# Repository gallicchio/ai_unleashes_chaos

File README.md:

# AI UNLEASHES CHAOS

[Lorenz Attractor Circuit](https://seti.harvard.edu/unusual_stuff/misc/lorenz.htm) by Paul Horowitz in KiCAD

"Claude, I want you to build a nice little present for Paul Horowitz, which could also live on as an open source project and a kit that people could build. Make a KiCAD 10 project, schematic, and PCB to implement [Paul's Lorenz Attractor Circuit](https://seti.harvard.edu/unusual_stuff/misc/lorenz.htm)."

<!-- GitHub strips <iframe> from READMEs, so a video cannot play in place;
     this is the thumbnail with a play button, linked to YouTube. -->
<p align="center">
  
  <br>
  <a href="https://youtu.be/pzk5cd-qo5U"><b>&#9654; Watch on YouTube</b></a>
</p>

<!-- GitHub will not play a video stored in the repository inline in a README,
     so this is an animated GIF of it, linked to the clip itself. -->
<p align="center">
  
  <br>
  <a href="docs/images/20261106_154352_video_analog_scope.mp4?raw=true"><b>&#9654; Download the scope video (9 MB mp4)</b></a>
</p>

In graduate school I worked with Paul Horowitz, of [Art of Electronics](https://artofelectronics.net/) fame. I even contributed a few bits and pieces to the 3rd edition. (I am thanked in the footnotes, one of which simply says, "Jason, again.") This project started by [asking Claude](CLAUDE_CODE_CHAT.md) the above question. Watch his reaction above. Also watch Paul's [Interview with Ladyada](https://www.youtube.com/watch?v=iCI3B5eT9NA) to get a sense for the guy.

**Only Prompts:**
As an experiment, the entire PCB, along with additions to Paul's original circuit were designed in a few
hours of [prompts to Claude Opus 5 Max](CLAUDE_CODE_CHAT.md). I only typed prompts.
I only used KiCAD to look at the output of Claude's [python scripts](scripts/), which generated everything else.

## What it is

A 100 x 100 mm, two-layer, USB-C-powered analog computer that solves

    dx/dt = s (y - x)          s = 10
    dy/dt = r x - y - x z      r = 21.3 .. 37.0, on a knob
    dz/dt = x y - b z          b = 8/3

in real time, continuously, with three op-amp integrators and two **MPY634**
analog multipliers — Paul's exact parts, in hand-solderable packages, so the
circuit stays literally his. Hang a scope on `x` and `z` in X-Y and the
attractor's "owl's face" appears within a second of power-up.

**Fun additions to Paul's original circuit:**

* **Four speeds on a DIP switch** — `fast!` (τ = 2.2 ms) through `slower!`
  (572 ms), the six sliders reading left to right as a two-digit binary
  number. At `slower!` you can follow the dot around a wing by eye.
* **An r knob.** 21.3 to 37.0 on a single-turn trimmer, which takes you from
  "the trace spirals into one wing and stops" through the bistable window at
  r ≈ 24.1–24.7 and Lorenz's own 28, to a tight fast orbit at 37. Its wiper is
  tied to one end of the track on purpose: grit under a wiper then means
  *maximum resistance*, never an open circuit.
* **A chaos lamp.** One RGB LED whose colour is the state vector. Red
  follows −y, green x and blue z, and two more resistors pull red's and
  blue's thresholds apart so the dies take turns instead of mixing to
  white: it is vivid nine-tenths of the time and visits every hue about
  equally. Rev A's lamp was picked from [660 rendered wirings](docs/lamp/)
  with an LED model the boards then proved wrong — it came out mostly blue —
  so rev B's was chosen again with a corrected model, from 6.7 million
  wirings; [the ten finalists play in real time](docs/lamp2/).
* **A real isolated ground split.** The DC/DC converter's isolation is
  actually used: analog ground and USB ground are separate pours with a 1 mm
  gap, bridged only by 1 M, 2.2 nF and a solder jumper, so no mains-referenced
  loop runs through a signal whose full scale is 2 V.
* **`SYNC IN X`.** A fourth BNC and a weight knob: feed it another board's `x`
  output and the two boards synchronise — chaotic synchronisation on the
  bench. Pull
  the cable and they diverge again from states that agreed to a few
  millivolts. The knob is linear in coupling strength from 0 to 10, with the
  locking threshold at about 70 % of rotation.
**Everything here is generated.** There is no hand-edited schematic or board:
`./make.py` writes the symbols, footprints, 3D models, schematic, placement,
routing, silkscreen, gerbers, BOM and CPL from Python, and then checks them.
147 circuit assertions read the exported netlist back and re-derive the
equations from the resistors that are really attached, and simulate the lamp
the netlist really builds; the QR codes on the
back are decoded out of the gerbers they were plotted into; and a clean clone
rebuilds every deliverable byte-identically.

The back carries the equations, the owl's face drawn from a real integration
of them, and QR codes to Paul's page and to this repository.

## Building it

Needs KiCad 10, and Python 3 with `numpy` and `Pillow`; `pdftoppm`
(poppler-utils) for the preview images.

```bash
git clone https://github.com/gallicchio/ai_unleashes_chaos.git

cd ai_unleashes_chaos

# Nothing to configure if kicad-cli is on your PATH, or if a KiCad 10
# AppImage is in ~/.local/bin, ~/Downloads, ~/Applications, ~/bin or /opt:
# the build finds it and mounts it for as long as it runs.  Otherwise:
export KICAD_APPIMAGE=$HOME/.local/bin/kicad-10.0.6-x86_64.AppImage
# ...or, for an AppImage you have already extracted:
# export KICAD_APPRUN=$HOME/.local/kicad10/AppDir/AppRun

./make.py                # build and check everything  (~40 s)
./make.py --clean        # delete everything it generates
```

Upload `out/lorenz/lorenz-gerbers.zip` and `-bom.csv` to a fab, with
`-cpl_jlc_corrected.csv` for the placements if that fab is JLCPCB and
`-cpl.csv` if it is anyone else — JLCPCB turns six of the parts differently
from KiCad, and the corrected file is the same placements with those angles
applied. Read **[docs/MANUFACTURING.md](docs/MANUFACTURING.md)** first: it
lists what to check in the fab's preview before you pay.

## More

* **[docs/DESIGN_NOTES.md](docs/DESIGN_NOTES.md)** — the circuit, every
  changed value and why, and how the lamp was chosen.
* **[docs/DESIGN_REVIEW.md](docs/DESIGN_REVIEW.md)** — the design reviews,
  including the bugs the checks caught.
* **[CLAUDE_CODE_CHAT.md](CLAUDE_CODE_CHAT.md)** — the entire conversation
  that produced this board, prompt by prompt.

Circuit by Paul Horowitz. Board by Jason Gallicchio and Claude Opus 5 Max.

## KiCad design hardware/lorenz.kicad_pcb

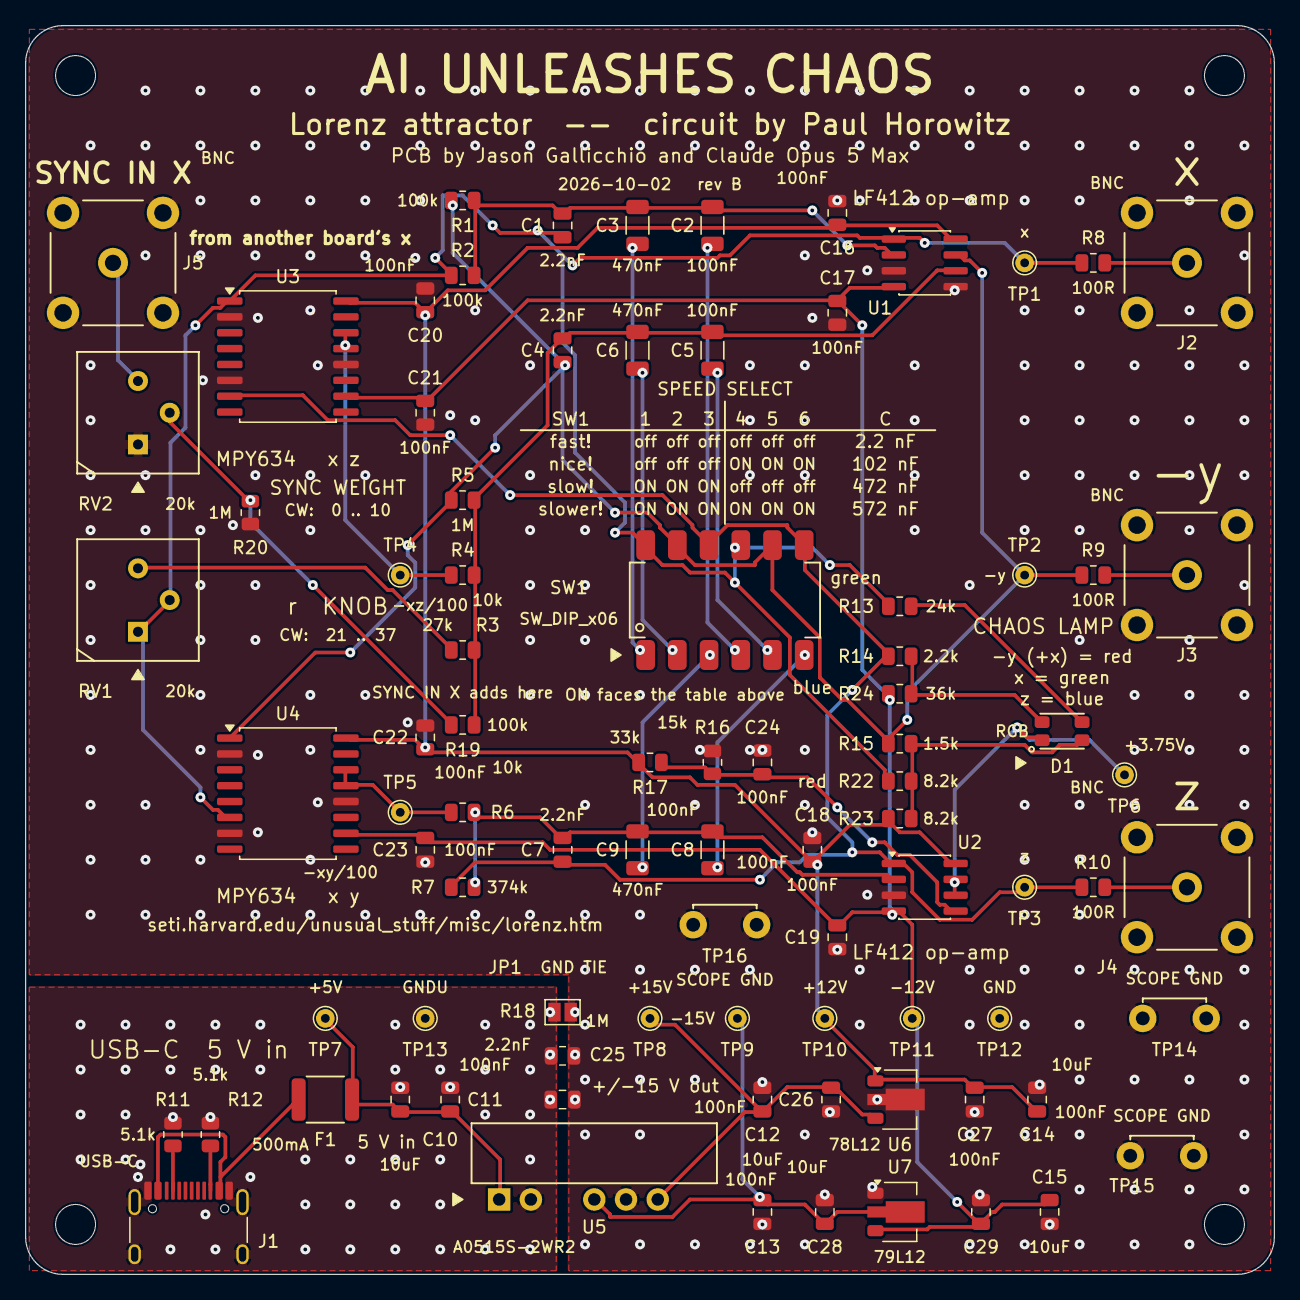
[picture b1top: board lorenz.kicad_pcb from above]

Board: 2 copper layers, 100.0 x 100.0 mm, 90 parts (0 on the bottom side), 35 nets.

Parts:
C1, C4, C7, C25: 2.2nF; C_0805_2012Metric
C2, C5, C8: 100nF; C_1206_3216Metric
C3, C6, C9: 470nF; C_1206_3216Metric
C10, C12, C13, C14, C15: 10uF; C_0805_2012Metric
C11, C16, C17, C18, C19, C20, C21, C22, C23, C24, C26, C27, C28, C29: 100nF; C_0805_2012Metric
D1: RGB; LED_RGB_PLCC4_3.5x2.8mm
F1: 500mA; PTC_1812_4532Metric
J1: USB-C; USB_C_Receptacle_HRO_TYPE-C-31-M-12
J2, J3, J4, J5: BNC; BNC_KYWE_RightAngle
JP1: GND TIE; SolderJumper-2_P1.3mm_Open_Pad1.0x1.5mm
MH1, MH2, MH3, MH4: MountingHole; MountingHole_3.2mm_M3
R1, R2, R19: 100k; R_0805_2012Metric
R3: 27k; R_0805_2012Metric
R4, R6: 10k; R_0805_2012Metric
R5, R18, R20: 1M; R_0805_2012Metric
R7: 374k; R_0805_2012Metric
R8, R9, R10: 100R; R_0805_2012Metric
R11, R12: 5.1k; R_0805_2012Metric
R13: 24k; R_0805_2012Metric
R14: 2.2k; R_0805_2012Metric
R15: 1.5k; R_0805_2012Metric
R16: 15k; R_0805_2012Metric
R17: 33k; R_0805_2012Metric
R22, R23: 8.2k; R_0805_2012Metric
R24: 36k; R_0805_2012Metric
RV1, RV2: 20k; Potentiometer_Bourns_3386P_Vertical
SW1: SW_DIP_x06; SW_DIP_SPSTx06_KingTek_DSIC06_P2.54mm
TP1: x; TestPoint_THTPad_D1.5mm_Drill0.7mm
TP2: -y; TestPoint_THTPad_D1.5mm_Drill0.7mm
TP3: z; TestPoint_THTPad_D1.5mm_Drill0.7mm
TP4: -xz/100; TestPoint_THTPad_D1.5mm_Drill0.7mm
TP5: -xy/100; TestPoint_THTPad_D1.5mm_Drill0.7mm
TP6: +3.75V; TestPoint_THTPad_D1.5mm_Drill0.7mm
TP7: +5V; TestPoint_THTPad_D1.5mm_Drill0.7mm
TP8: +15V; TestPoint_THTPad_D1.5mm_Drill0.7mm
TP9: -15V; TestPoint_THTPad_D1.5mm_Drill0.7mm
TP10: +12V; TestPoint_THTPad_D1.5mm_Drill0.7mm
TP11: -12V; TestPoint_THTPad_D1.5mm_Drill0.7mm
TP12: GND; TestPoint_THTPad_D1.5mm_Drill0.7mm
TP13: GNDU; TestPoint_THTPad_D1.5mm_Drill0.7mm
TP14, TP15, TP16: SCOPE GND; TestPoint_ScopeGnd_Loop_2x1.1mm
U1, U2: LF412; SOIC-8_3.9x4.9mm_P1.27mm
U3, U4: MPY634; SOIC-16W_7.5x10.3mm_P1.27mm
U5: A0515S-2WR2; DCDC_SIP_A05xxS_1W_2W
U6: 78L12; SOT-89-3
U7: 79L12; SOT-89-3

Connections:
+5V: C10.1, C11.1, F1.2, TP7.1, U5.1
+12V: C14.1, C16.1, C18.1, C20.1, C22.1, C27.2, R17.1, R23.2, TP10.1, U1.8, U2.8, U3.16, U4.16, U6.1
+15V: C12.1, C26.2, TP8.1, U5.6, U6.3
-12V: C15.2, C17.2, C19.2, C21.2, C23.2, C29.1, R24.2, TP11.1, U1.4, U2.4, U3.10, U4.10, U7.3
-15V: C13.2, C28.1, TP9.1, U5.4, U7.2
/-y: C4.1, R1.1, R5.1, R9.1, R15.2, SW1.8, SW1.11, TP2.1, U1.7, U4.1
/SJ_X: C1.2, C2.2, C3.2, R1.2, R2.2, U1.2
/SJ_Y: C4.2, C5.2, C6.2, R3.2, R4.2, R5.2, R19.2, U1.6
/SJ_Z: C7.2, C8.2, C9.2, R6.2, R7.2, U2.2
/x: C1.1, R2.1, R8.1, R13.2, R22.2, RV1.1, RV1.2, SW1.9, SW1.12, TP1.1, U1.1, U3.1, U4.6
/xy: R6.1, TP5.1, U4.13, U4.14
/xz: R4.1, TP4.1, U3.13, U3.14
/z: C7.1, R7.1, R10.1, R14.2, SW1.7, SW1.10, TP3.1, U2.1, U3.7
GND: C12.2, C13.1, C14.2, C15.1, C16.2, C17.1, C18.2, C19.1, C20.2, C21.1, C22.2, C23.1, C24.2, C25.2, C26.1, C27.1, C28.2, C29.2, J2.2, J3.2, J4.2, J5.2, JP1.2, R16.2, R18.2, R20.1, RV2.1, TP12.1, TP14.1, TP15.1, TP16.1, U1.3, U1.5, U2.3, U3.2, U3.6, U3.12, U4.2, U4.7, U4.12, U5.5, U6.2, U7.1
GNDU: C10.2, C11.2, C25.1, J1.A1, J1.A12, J1.B1, J1.B12, J1.SH, JP1.1, R11.2, R12.2, R18.1, TP13.1, U5.2
unnamed: C2.1, SW1.4
unnamed: C3.1, SW1.1
unnamed: C5.1, SW1.5
unnamed: C6.1, SW1.2
unnamed: C8.1, SW1.6
unnamed: C9.1, SW1.3
unnamed: D1.1, TP6.1, U2.6, U2.7
unnamed: D1.2, R14.1, R24.1
unnamed: D1.3, R13.1
unnamed: D1.4, R15.1, R22.1, R23.1
unnamed: F1.1, J1.A4, J1.A9, J1.B4, J1.B9
unnamed: J1.A5, R11.1
unnamed: J1.B5, R12.1
unnamed: J2.1, R8.2
unnamed: J3.1, R9.2
unnamed: J4.1, R10.2
unnamed: J5.1, RV2.3
unnamed: R3.1, RV1.3
unnamed: R19.1, R20.2, RV2.2
unnamed: C24.1, R16.1, R17.2, U2.5

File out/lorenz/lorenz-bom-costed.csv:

Comment,Designator,Footprint,LCSC Part #,MPN,Qty,Unit $,Ext $,JLC
100nF,"C2,C5,C8",C_1206_3216Metric,C170182,1206N104J500CT,3,0.1870,0.561,extended
470nF,"C3,C6,C9",C_1206_3216Metric,C277483,CC1206KKX7R9BB474,3,0.0320,0.096,extended
2.2nF,"C1,C4,C7,C25",C_0805_2012Metric,C28260,CL21C222JBFNNNE,4,0.0280,0.112,basic
10uF,"C10,C12,C13,C14,C15",C_0805_2012Metric,C15850,CL21A106KAYNNNE,5,0.0840,0.420,basic
100nF,"C11,C16,C17,C18,C19,C20,C21,C22,C23,C24,C26,C27,C28,C29",C_0805_2012Metric,C49678,CC0805KRX7R9BB104,14,0.0190,0.266,basic
RGB,D1,LED_RGB_PLCC4_3.5x2.8mm,C2962095,MHPA3528CRGBCT,1,0.0650,0.065,extended
500mA,F1,PTC_1812_4532Metric,C17313,MF-MSMF050-2,1,0.0680,0.068,extended
USB-C,J1,USB_C_Receptacle_HRO_TYPE-C-31-M-12,C165948,TYPE-C-31-M-12,1,0.1860,0.186,extended
BNC,"J2,J3,J4,J5",BNC_KYWE_RightAngle,C41416668,BNC-KYWE-295-W4-N,4,1.5490,6.196,extended
27k,R3,R_0805_2012Metric,C17593,0805W8F2702T5E,1,0.0013,0.001,basic
374k,R7,R_0805_2012Metric,C2933427,FRC0805F3743TS,1,0.0040,0.004,extended
24k,R13,R_0805_2012Metric,C17575,0805W8F2402T5E,1,0.0021,0.002,basic
2.2k,R14,R_0805_2012Metric,C17520,0805W8F2201T5E,1,0.0021,0.002,basic
1.5k,R15,R_0805_2012Metric,C4310,0805W8F1501T5E,1,0.0015,0.002,basic
15k,R16,R_0805_2012Metric,C17475,0805W8F1502T5E,1,0.0021,0.002,basic
33k,R17,R_0805_2012Metric,C17633,0805W8F3302T5E,1,0.0028,0.003,basic
36k,R24,R_0805_2012Metric,C4360,0805W8F3602T5E,1,0.0029,0.003,basic
10k,"R4,R6",R_0805_2012Metric,C17414,0805W8F1002T5E,2,0.0040,0.008,basic
5.1k,"R11,R12",R_0805_2012Metric,C27834,0805W8F5101T5E,2,0.0060,0.012,basic
8.2k,"R22,R23",R_0805_2012Metric,C17828,0805W8F8201T5E,2,0.0021,0.004,basic
20k,"RV1,RV2",Potentiometer_Bourns_3386P_Vertical,C116287,3386P-1-203LF,2,0.4458,0.892,extended
100k,"R1,R2,R19",R_0805_2012Metric,C149504,0805W8F1003T5E,3,0.0060,0.018,basic
100R,"R8,R9,R10",R_0805_2012Metric,C17408,0805W8F1000T5E,3,0.0040,0.012,basic
1M,"R5,R18,R20",R_0805_2012Metric,C17514,0805W8F1004T5E,3,0.0050,0.015,basic
SW_DIP_x06,SW1,SW_DIP_SPSTx06_KingTek_DSIC06_P2.54mm,C54952,DSIC06LSGET,1,0.5710,0.571,extended
A0515S-2WR2,U5,DCDC_SIP_A05xxS_1W_2W,C19272710,A0515S-2WR2,1,1.5950,1.595,extended
78L12,U6,SOT-89-3,C8615,CJ78L12,1,0.0990,0.099,extended
79L12,U7,SOT-89-3,C8626,CJ79L12,1,0.1180,0.118,extended
LF412,"U1,U2",SOIC-8_3.9x4.9mm_P1.27mm,C15322,LF412CDR,2,0.9060,1.812,extended
MPY634,"U3,U4",SOIC-16W_7.5x10.3mm_P1.27mm,C1523457,MPY634KU/1K,2,30.5860,61.172,extended

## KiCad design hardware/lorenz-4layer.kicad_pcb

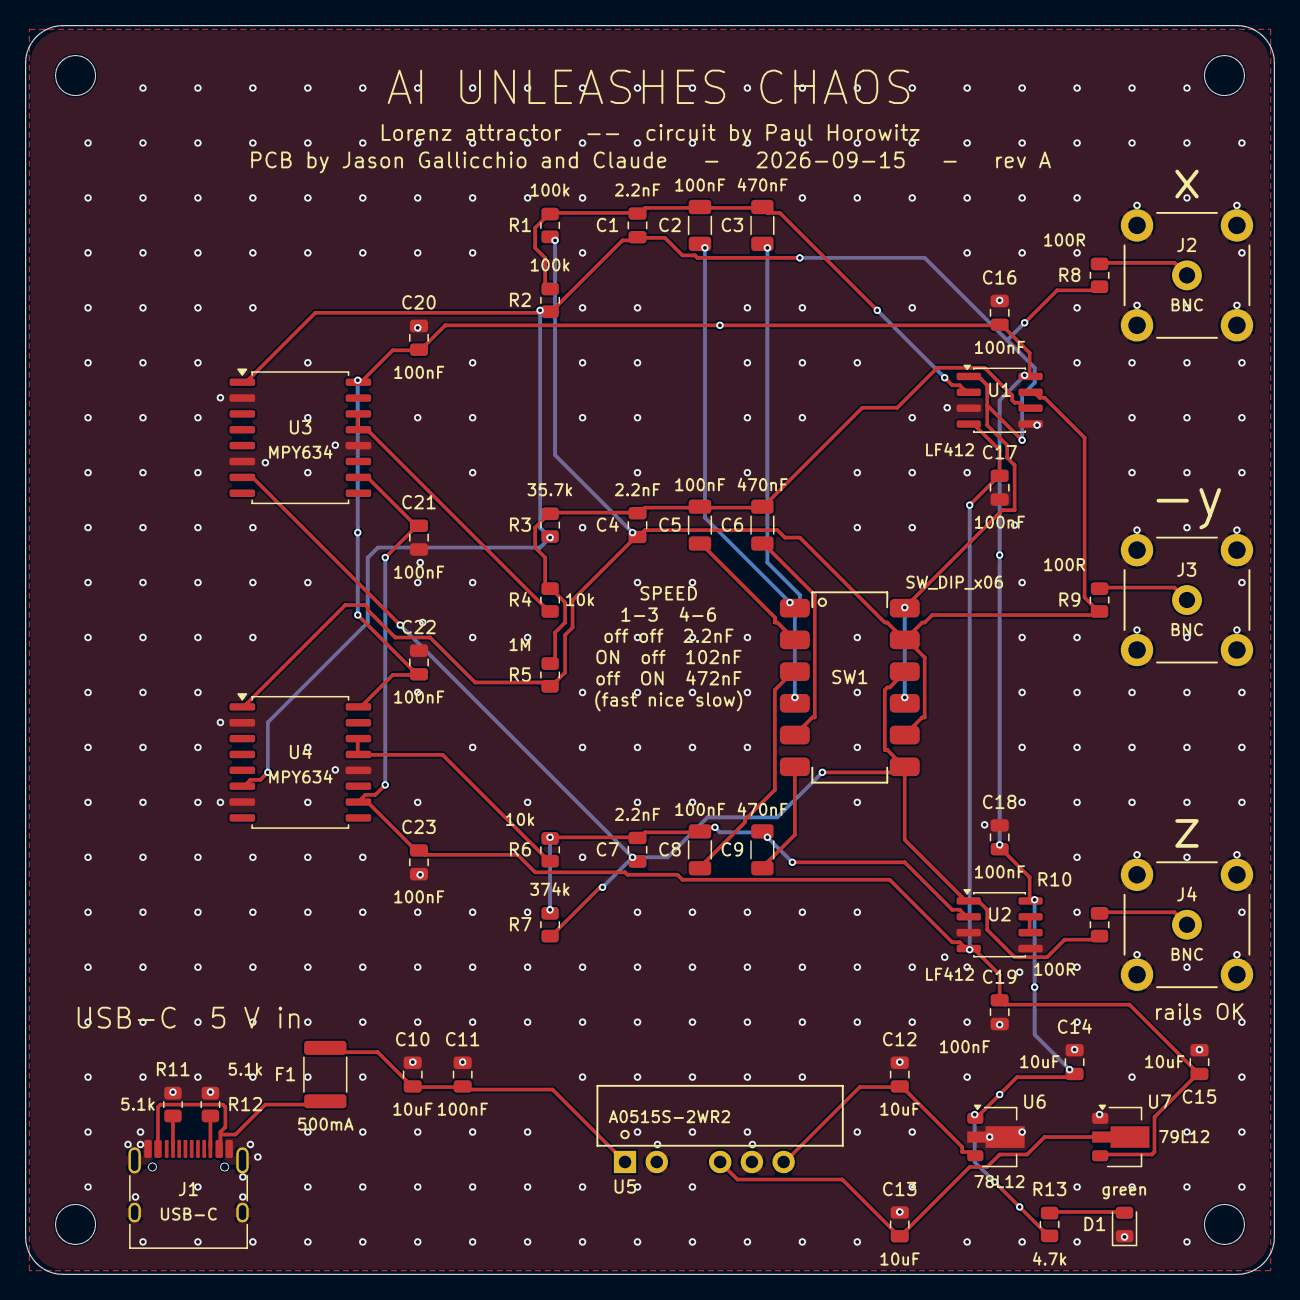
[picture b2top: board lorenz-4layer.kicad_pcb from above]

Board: 4 copper layers, 100.0 x 100.0 mm, 54 parts (0 on the bottom side), 28 nets.

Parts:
C1, C4, C7: 2.2nF; C_0805_2012Metric
C2, C5, C8: 100nF; C_1206_3216Metric
C3, C6, C9: 470nF; C_1206_3216Metric
C10, C12, C13, C14, C15: 10uF; C_0805_2012Metric
C11, C16, C17, C18, C19, C20, C21, C22, C23: 100nF; C_0805_2012Metric
D1: green; LED_0805_2012Metric
F1: 500mA; Fuse_1812_4532Metric
J1: USB-C; USB_C_Receptacle_HRO_TYPE-C-31-M-12
J2, J3, J4: BNC; BNC_KYWE_RightAngle
MH1, MH2, MH3, MH4: MountingHole; MountingHole_3.2mm_M3
R1, R2: 100k; R_0805_2012Metric
R3: 35.7k; R_0805_2012Metric
R4, R6: 10k; R_0805_2012Metric
R5: 1M; R_0805_2012Metric
R7: 374k; R_0805_2012Metric
R8, R9, R10: 100R; R_0805_2012Metric
R11, R12: 5.1k; R_0805_2012Metric
R13: 4.7k; R_0805_2012Metric
SW1: SW_DIP_x06; SW_DIP_SPSTx06_KingTek_DSIC06_P2.54mm
U1, U2: LF412; SOIC-8_3.9x4.9mm_P1.27mm
U3, U4: MPY634; SOIC-16W_7.5x10.3mm_P1.27mm
U5: A0515S-2WR2; DCDC_SIP_A05xxS_1W_2W
U6: 78L12; SOT-89-3
U7: 79L12; SOT-89-3

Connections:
+5V: C10.1, C11.1, F1.2, U5.1
+12V: C14.1, C16.1, C18.1, C20.1, C22.1, R13.1, U1.8, U2.8, U3.16, U4.16, U6.1
+15V: C12.1, U5.6, U6.3
-12V: C15.1, C17.2, C19.2, C21.2, C23.2, U1.4, U2.4, U3.10, U4.10, U7.3
-15V: C13.1, U5.4, U7.2
/-y: C4.1, R1.1, R5.1, R9.1, SW1.8, SW1.11, U1.7, U4.1
/x: C1.1, R2.1, R3.1, R8.1, SW1.9, SW1.12, U1.1, U3.1, U4.6
/xy: R6.1, U4.13, U4.14
/xz: R4.1, U3.13, U3.14
/z: C7.1, R7.1, R10.1, SW1.7, SW1.10, U2.1, U3.7
GND: C10.2, C11.2, C12.2, C13.2, C14.2, C15.2, C16.2, C17.1, C18.2, C19.1, C20.2, C21.1, C22.2, C23.1, D1.1, J1.A1, J1.A12, J1.B1, J1.B12, J1.SH, J2.2, J3.2, J4.2, R11.2, R12.2, U1.3, U1.5, U2.3, U2.5, U3.2, U3.6, U3.12, U4.2, U4.7, U4.12, U5.2, U5.5, U6.2, U7.1
unnamed: C2.1, SW1.1
unnamed: C3.1, SW1.4
unnamed: C5.1, SW1.2
unnamed: C6.1, SW1.5
unnamed: C8.1, SW1.3
unnamed: C9.1, SW1.6
unnamed: D1.2, R13.2
unnamed: F1.1, J1.A4, J1.A9, J1.B4, J1.B9
unnamed: J1.A5, R11.1
unnamed: J1.B5, R12.1
unnamed: J2.1, R8.2
unnamed: J3.1, R9.2
unnamed: J4.1, R10.2
unnamed: C1.2, C2.2, C3.2, R1.2, R2.2, U1.2
unnamed: C4.2, C5.2, C6.2, R3.2, R4.2, R5.2, U1.6
unnamed: C7.2, C8.2, C9.2, R6.2, R7.2, U2.2
unnamed: U2.6, U2.7

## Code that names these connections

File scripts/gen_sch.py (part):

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            opa=("U1", 1), out="x", y=ROW_Y[0],
            res=[("R1", "100k", -6.35, "-y"), ("R2", "100k", +6.35, "x")],
            caps=("C1", "C2", "C3"), poles=(4, 1), outres="R8", bnc="J2",
            label="x", sj="SJ_X", colour="green", die="3", note="dx/dt = 10 (y - x)"),
        dict(  # dy/dt = 28x - y - xz
            opa=("U1", 2), out="-y", y=ROW_Y[1],
            res=[("R5", "1M", -19.05, "-y"), ("R4", "10k", -12.7, "xz"),
                 ("R3", "27k", 0.0, "x")],
            caps=("C4", "C5", "C6"), poles=(5, 2), outres="R9", bnc="J3",
            label="-y", sj="SJ_Y", colour="blue", die="2", note="dy/dt = r x - y - x z"),
        dict(  # dz/dt = xy - (8/3) z
            opa=("U2", 1), out="z", y=ROW_Y[2],
            res=[("R6", "10k", -6.35, "xy"), ("R7", "374k", +6.35, "z")],
            caps=("C7", "C8", "C9"), poles=(6, 3), outres="R10", bnc="J4",
            label="z", sj="SJ_Z", colour="red", die="4", note="dz/dt = x y - 2.674 z"),
    ]

    feeds = {"x": [], "-y": [], "z": []}      # (x_start, y) horizontal bus taps
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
